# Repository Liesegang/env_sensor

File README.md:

# Environment sensors

機種ごとに回路・ファームウェア・受信アプリ・プロトコルをまとめる。

```text
card/
  hardware/       v1 KiCad / v2 Fusionの回路・基板・3Dモデル
  firmware/       nRF54L15 / Zephyr
  software/       SwiftUI / iPhoneのBLE収集・履歴アプリ
outdoor/
  hardware/       env_sensor_3の回路・基板
  firmware/       nRF54L15 / Zephyr
  software/       TypeScript / ReactのWeb BLE受信アプリ
  protocol/       共通BLEスキーマへの互換入口
shared/
  firmware/driver/     cardとoutdoor共通のセンサー・表示ドライバー
  firmware/telemetry/  共通BLEエンコーダー・GATT通信
  protocol/           BLEの共通スキーマ・C / TypeScript / Swiftコード生成
room/
  hardware/       env_sensor_1aの回路・基板
docs/
  datasheets/     機種共通のメーカー資料
```

Outdoorの開発・検証は[ファームウェア](outdoor/firmware/README.md)、
[Web受信アプリ](outdoor/software/README.md)、[BLE仕様](outdoor/protocol/README.md)を参照。
[Card firmware](card/firmware/README.md)はv2基板で毎分測定・BLE送信、
10分ごとのSD一括記録、1時間ごとの電子ペーパー更新を行う。
[iPhoneアプリ](card/software/README.md)は共通BLEで受信し、バックグラウンド収集・端末内の履歴保存・JSON / CSV書き出しを行う。
資料の一覧は[データシート](docs/datasheets/README.md)にある。

BMV080のIC9はセンサーpinとコネクターpadの対応が反転している。
[配線の照合結果](outdoor/hardware/BMV080-pin-review.md)を参照。回路・基板の配線は未修正。

リポジトリのルートから実行する：

```sh
python3 outdoor/protocol/generate.py --check
outdoor/firmware/scripts/fw test
cd outdoor/software
npm ci
npm run dev
```

ファームウェアのSDK、バックアップ、実機ログは`outdoor/firmware/.local/`へ保存し、Gitに含めない。

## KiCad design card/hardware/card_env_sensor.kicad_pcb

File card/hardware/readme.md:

# card_env_sensor

## v2（現行）

`v2/card_env_sensor_1.fsch` / `.fbrd` の部品と配線。実装型番はシンボル名より
部品の`PARTS`属性とユーザーの確認を優先する。

| 部品 | シンボル / `PARTS`の実装指定 | I²Cアドレス | 備考 |
| --- | --- | ---: | --- |
| IC2 | OPT4001DTSR | `0x45` | 照度。ADDRは`+V`接続 |
| IC11 | BME688 / **BME690** | `0x76` | 温湿度・気圧・ガス抵抗 |
| IC6 | SGP40-D-R4 / **SPG41**（SGP41の表記違い） | `0x59` | VOC・NOx |
| IC12 | STCC4-D-R3 | `0x64` | CO₂ |
| U1 | nPM1300-QEAA-R | `0x6B` | 電源管理 |
| IC1 | SFA40 | `0x5D` | 回路にはあるが今回の実機には未実装 |
| IC7 | SHT40-BD1B-R2 / **SHT4x-Axx**（実装SHT45） | 補助バス`0x44` | STCC4専用のSCL_C/SDA_Cへ接続 |

MCU IC5はES4L15BA1 / nRF54L15。メインI²CはP0.03（SCL）とP0.04（SDA）。
P1.00の`ENABLE`をLowにするとFET3がオンになり、センサーとI²Cプルアップの電源`+V`が入る。
P1.01の`BUZZER`はTR1経由でブザーを駆動する。P1.00/P1.01を使用するためLFXOは使えない。
IC2の電源デカップリングC36は0.1 µF、SCL/SDAのプルアップR12/R13は各5.1 kΩ。

SHT45はMCUのメインバスから直接読まない。STCC4の自己診断で補助バス上の
接続を確認し、STCC4の測定値に含まれる温湿度を使う。

## v1（旧KiCad設計）

### I²C アドレス

アドレスは R/W ビットを含まない 7-bit 表記である。

回路図のアドレス選択端子の接続を反映した通信先は次のとおり。

| リファレンス | デバイス | I²C アドレス | アドレスの決定条件 | 資料箇所 |
| --- | --- | ---: | --- | ---: |
| IC3 | [BME690](../../docs/datasheets/BME690_datasheet.pdf) | `0x76` | `SDO = GND`。`SDO = VDDIO` では `0x77` | p. 46 |
| IC4 | [SGP41-D-R4](../../docs/datasheets/Sensirion_Gas_Sensors_Datasheet_SGP41.pdf) | `0x59` | 固定 | p. 12 |
| IC5 | [STCC4-D-R3](../../docs/datasheets/CD_DS_STCC4_D1.pdf) | `0x64` | `ADDR = GND`。`ADDR = VDD` では `0x65` | p. 5 |
| U1 | [SHT45](../../docs/datasheets/HT_DS_Datasheet_SHT4x_5.pdf) | `0x44` | 固定。STCC4 の SHT4x 接続用バスに接続 | p. 1 |
| IC6 | [SFA40](../../docs/datasheets/Sensirion_Datasheet_SFA40.pdf) | `0x5D` | 固定 | p. 7 |
| IC7 | [OPT4001YMNR](../../docs/datasheets/opt4001.pdf) | `0x45` | YMN（PicoStar）パッケージで固定 | p. 21 |
| IC2 | [nPM1300-QEXX](../../docs/datasheets/nPM1300_PS_v1.3.pdf) | `0x6B` | 固定 | p. 125 |

> [!NOTE]
> SHT45（U1）はメインの `SCL` / `SDA` バスではなく、STCC4（IC5）の SHT4x 接続用バス `SCL_C` / `SDA_C` に接続されている。
> ホストは SHT45 をメインバスから直接アドレス指定せず、STCC4 内蔵の I²C コントローラーが SHT45 と通信する。

### ほかの I²C 接続

回路図上で I²C ターゲットとして接続されているデバイスは、上表の7個だけである。

IC1 はホスト側のコントローラーであり、I²C ターゲットには数えない。

e-Paper コネクタ（CON2）の `TSCL` と `TSDA` は未接続である。

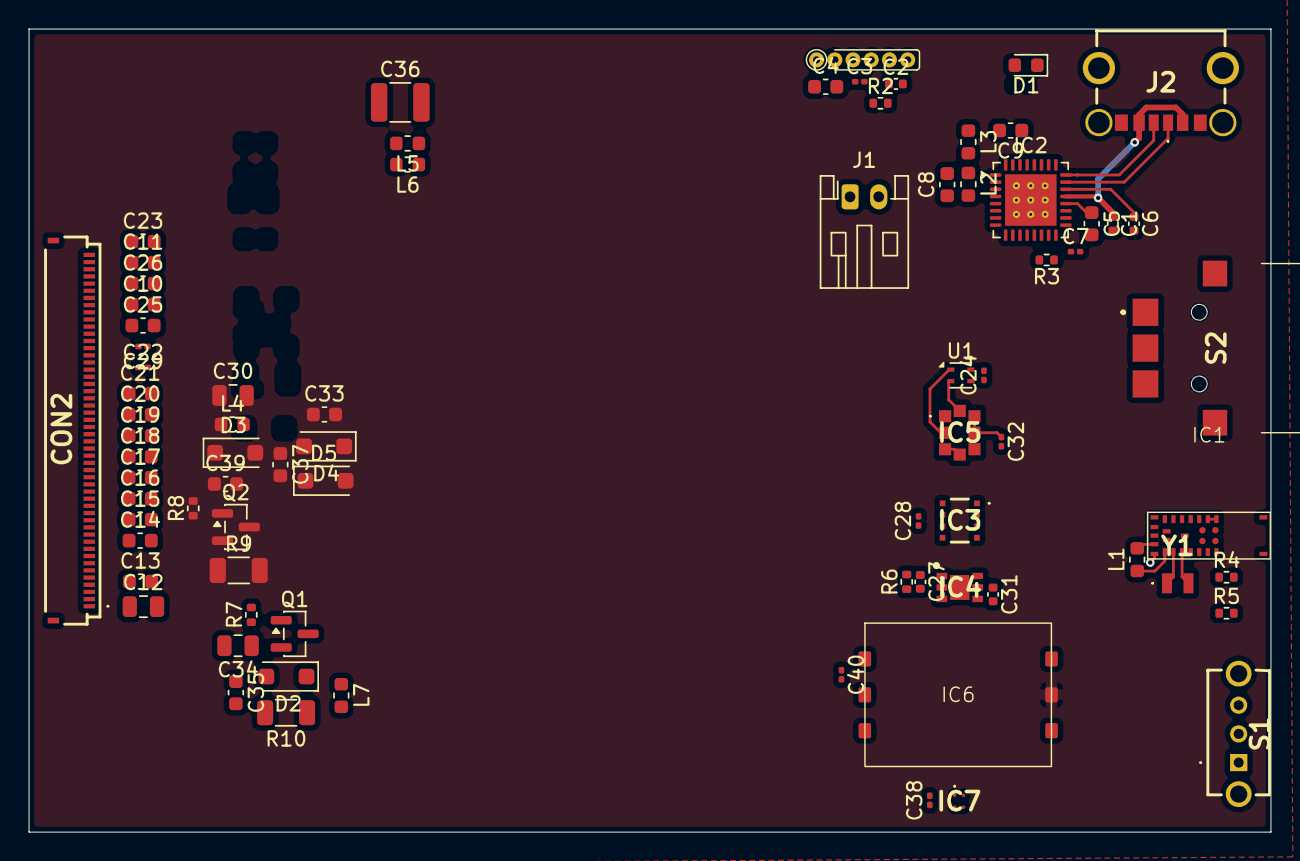
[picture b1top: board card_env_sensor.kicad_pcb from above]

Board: 2 copper layers, 86.6 x 56.0 mm, 78 parts (0 on the bottom side), 66 nets.

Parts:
C1, C2, C6, C27, C31: 1u; C_0402_1005Metric
C3, C24, C28, C32, C38, C40: 0.1u; C_0201_0603Metric
C4, C5, C8, C9: 10u; C_0603_1608Metric
C7: 2.2u; C_0201_0603Metric
C10, C11, C20, C21, C25, C26: 1u/50V; C_0603_1608Metric
C12, C30, C34: 4.7u/25V; C_0805_2012Metric
C13, C23: 470n/25V; C_0603_1608Metric
C14, C15, C16, C17, C18, C19, C33, C35, C37, C39: 10u/25V; C_0603_1608Metric
C22: 2.2u/6.3V; C_0201_0603Metric
C29: 0.1u/50V; C_0201_0603Metric
C36: 100u/6.3V; C_1210_3225Metric
CON1: PINH6IDC
CON2: FH34SRJ50S05SH50
D1: LED; LED_0603_1608Metric
D2, D3, D4, D5: RB160M-30TR; D_SOD-123F
IC1: ES4L15BA1
IC2: nPM1300-QEXX; QFN-32-1EP_5x5mm_P0.5mm_EP3.6x3.6mm_ThermalVias
IC3: BME690
IC4: SGP41-D-R4; SON80P244X244X95-7N
IC5: STCC4-D-R3; STCC4DR3
IC6: SFA40
IC7: OPT4001YMNR
J1: Conn_01x02; JST_PH_S2B-PH-K_1x02_P2.00mm_Horizontal
J2: UJC-HP-3-SMT-TR; UJCHP3SMTTR
L1: 4.7uH; L_0603_1608Metric
L2, L3: 2.2uH; L_0603_1608Metric
L4, L7: 10uH; L_0603_1608Metric
L5, L6: BLM18PG121SN1D; L_0603_1608Metric
Q1: IRLML6402; SOT-23
Q2: IRLML6344TRPBFTR; SOT-23
R2, R4, R5: 10k; R_0402_1005Metric
R3: 150k; R_0402_1005Metric
R6: 4.7; R_0402_1005Metric
R7, R8: 1M; R_0402_1005Metric
R9, R10: 0.2R; R_1206_3216Metric
S1: SK-12D11VG3; SK12D11VG3
S2: TMHU27
U1: SHT4x; Sensirion_DFN-4_1.5x1.5mm_P0.8mm_SHT4x_NoCentralPad
Y1: 32.768k; FC12M327680KDA0

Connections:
/BSY_N: CON2.29 (BUSY_N), IC1.20 (P1.08/EXTREF)
/CSN: CON2.31 (CSB1), IC1.5 (P1.03/NFC2)
/DCX: CON2.30 (DC), IC1.16 (P1.05/AIN1)
/EPD_3V: C29.2, CON2.38 (VDD), CON2.40 (VDDIO), L5.2
/GDRC: CON2.9 (GDRC), Q1.1 (G), R7.2
/GDRH: CON2.5 (GDRH), Q2.1 (G), R8.1
/LED1: D1.1 (K), IC2.26 (LED1)
/NRST: C2.1, CON1.1, IC1.6 (nRESET), R2.1
/RESEC: CON2.10 (RESEC), L7.2, R10.1
/RESEH: CON2.6 (RESEH), Q2.2 (S), R9.1
/RST_N: CON2.28 (RST_N), IC1.22 (P1.07/AIN3)
/SCK: CON2.32 (SCL), IC1.17 (P1.04/AIN0)
/SCL: IC1.8 (P0.03), IC2.14 (SCL), IC3.4 (SCK), IC4.6 (SCL), IC5.1 (SCL), IC6.3 (SCL), IC7.A2 (SCL), R4.2
/SDA: IC1.7 (P0.04), IC2.13 (SDA), IC3.3 (SDI), IC4.3 (SDA), IC5.5 (SDA), IC6.4 (SDA), IC7.B2 (SDA), R5.2
/SDO: CON2.33 (SI0), IC1.25 (P1.06/AIN2)
/SWCLK: CON1.5, IC1.15 (SWDCLK)
/SWDIO: CON1.3, IC1.14 (SWDIO)
/VGH: C39.1, CON2.14 (VPH), CON2.49 (VGH), D3.1 (K)
/VGL: C37.1, CON2.13 (VGL), D4.2 (A)
/VOU1: C8.2, IC2.1 (VOUT1), L2.1, L5.1, L6.1
/VOU2: C9.2, IC2.12 (VDDIO), IC2.32 (VOUT2), L3.1, S1.2
/VPC: C35.1, CON2.11 (VPC), D2.2 (A)
/VSYS: C5.1, D1.2 (A), IC2.4 (PVDD), IC2.20 (VSYS)
/V_B: C30.1, C34.1, C36.1, L4.1, L6.2, Q1.2 (S), R7.1
GND: C1.2, C2.2, C3.2, C4.2, C5.2, C6.2, C7.2, C8.1, C9.1, C12.2, C13.2, C14.2, C15.2, C16.2, C17.2, C18.2, C19.2, C20.2, C21.2, C22.2, C23.2, C24.2, C25.2, C26.2, C27.2, C28.2, C29.1, C30.2, C31.2, C32.2, C34.2, C35.2, C36.2, C37.2, C38.2, C39.2, C40.2, CON1.4, CON2.8 (GND), CON2.12 (GND), CON2.21 (GNDA+(GND)), CON2.26 (BS0), CON2.27 (BS1), CON2.39 (GND), CON2.51 (MP1), CON2.52 (MP2), D5.1 (K), IC1.1 (GND), IC1.13 (GND), IC1.18 (GND), IC2.2 (PVSS1), IC2.6 (PVSS2), IC2.17 (VSET1), IC2.18 (NTC), IC2.28 (LSIN1/VINLDO1), IC2.29 (LSOUT1/VOUTLDO1), IC2.30 (LSIN2/VINLDO2), IC2.31 (LSOUT2/VOUTLDO2), IC2.33 (AVSS), IC3.1 (GND_1), IC3.5 (SDO), IC3.7 (GND_2), IC4.2 (VSS), IC4.4 (N/A), IC4.7 (EP), IC5.3 (ADDR), IC5.4 (VSS), IC6.2 (VSS), IC6.6 (VSS), IC7.A1 (GND), J1.1, J2.A12 (GND_1), J2.B12 (GND_2), J2.MH1, J2.MH2, J2.MH3, J2.MH4, R3.1, R8.2, R9.2, R10.2, S1.MH1, S1.MH2, S2.MP1, S2.MP2, U1.4 (VSS)
unnamed: C11.1, CON2.45 (CP1N)
unnamed: C11.2, CON2.46 (CP1P)
unnamed: C10.1, CON2.42 (CP2N)
unnamed: C10.2, CON2.43 (CP2P)
unnamed: C13.1, CON2.3 (FPL_VCOM)
unnamed: C20.1, CON2.22 (REFN)
unnamed: C21.1, CON2.23 (REFP)
unnamed: C12.1, CON2.2 (TFT_VCOM)
unnamed: C23.1, CON2.50 (VCOMBD)
unnamed: C26.1, CON2.44 (VCP1)
unnamed: C25.1, CON2.41 (VCP2)
unnamed: C22.1, CON2.37 (VDDDO)
unnamed: C14.1, CON2.15 (VSH)
unnamed: C16.1, CON2.17 (VSH_LV2)
unnamed: C15.1, CON2.16 (VSH_LV)
unnamed: C17.1, CON2.18 (VSL)
unnamed: C19.1, CON2.20 (VSL_LV2)
unnamed: C18.1, CON2.19 (VSL_LV)
unnamed: D2.1 (K), L7.1, Q1.3 (D)
unnamed: C33.1, D3.2 (A), L4.2, Q2.3 (D)
unnamed: C33.2, D4.1 (K), D5.2 (A)
unnamed: IC1.21 (DCC), L1.2
unnamed: IC1.2 (DECD), L1.1
unnamed: IC1.11 (OUT_ANT), IC1.12 (OUT_MOD)
unnamed: IC1.4 (P1.00/XL1), Y1.2
unnamed: IC1.3 (P1.01/XL2), Y1.1
unnamed: IC1.10 (P2.01), S2.1
unnamed: IC1.23 (P2.02), S2.2
unnamed: IC1.24 (P2.05), S2.T1
unnamed: IC2.23 (CC1), J2.A5 (CC1)
unnamed: IC2.24 (CC2), J2.B5 (CC2)
unnamed: IC2.3 (SW1), L2.2
unnamed: IC2.5 (SW2), L3.2
unnamed: C6.1, IC2.22 (VBUSOUT)
unnamed: IC2.16 (VSET2), R3.2
unnamed: C27.1, IC4.1 (VDD), R6.2
unnamed: IC5.8 (SCL_C), U1.2 (SCL)
unnamed: IC5.2 (SDA_C), U1.1 (SDA)
VBAT: C7.1, IC2.19 (VBAT), J1.2
VBUS: C1.1, IC2.21 (VBUS), J2.A9 (V-BUS_1), J2.B9 (V-BUS_2)
VCC: C3.1, C4.1, C24.1, C28.1, C31.1, C32.1, C38.1, C40.1, CON1.2, IC1.19 (VDD), IC3.2 (CSB), IC3.6 (VDDIO), IC3.8 (VDD), IC4.5 (VDDH), IC5.6 (VDDIO), IC5.7 (VDD), IC6.1 (VDD), IC7.B1 (VDD), R2.2, R4.1, R5.1, R6.1, S1.1, U1.3 (VDD)
